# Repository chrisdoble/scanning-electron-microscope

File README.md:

This repository contains my DIY scanning electron microscope project.

My initial goal is to image samples using secondary electron emission and control the microscope from my computer.

I'm also documenting the process on YouTube [here](https://www.youtube.com/playlist?list=PLmlXFuUXRl5AR0MqcsTuL44zxy5YJyGKN).

# Roadmap

- [x] Purchase vacuum equipment
  - Edwards ADC MkII gauge controller
  - Edwards WRG-S wide range pressure gauge
  - Pfeiffer TC-600 turbomolecular pump controller
  - Pfeiffer TMH 071 P turbomolecular pump
- [x] Build a controller for the vacuum equipment
- [ ] Build a filament characterisation system
- [ ] Build an electron gun
- [ ] Build electrostatic or electromagnetic lenses
- [ ] Build an Everhart-Thornley detector
- [ ] ???
- [ ] Look at stuff

# Repository structure

The repository structure is as follows:

- [`controller`](controller): Contains files relating to the controller hardware that enables communication with the vacuum equipment, controls relays, etc.
- [`common`](common): A Rust crate containing code common to `firmware` and `host`.
- [`electron-gun-simulation`](electron-gun-simulation): A web-based simulation of an electron gun.
- [`filament-characterisation`](filament-characterisation): Contains files relating to the hardware and software used to characterise tungsten filaments to be used in the SEM.
- [`host`](host): A Rust crate containing both a library for interfacing with the controller hardware (pressure gauge, turbo molecular pump, etc.) and a binary for doing the same via a TUI.
- [`usb-tmc`](usb-tmc): A Rust crate containing an implementation of the [USB Test and Measurement Class](https://www.usb.org/document-library/test-measurement-class-specification) for interfacing with oscilloscopes, power supplies, etc.

# Required hardware

- A [Rigol DHO-814 oscilloscope](https://core-electronics.com.au/rigol-dho-814-oscilloscope.html)
- A [Rigol DP-932E power supply](https://core-electronics.com.au/rigol-dp-932e-triple-output-dc-power-supply.html)
- The custom controller as detailed in the [`controller`](controller) directory.
- The vacuum equipment mentioned above

# Running

See each directory's `README.md` for instructions.

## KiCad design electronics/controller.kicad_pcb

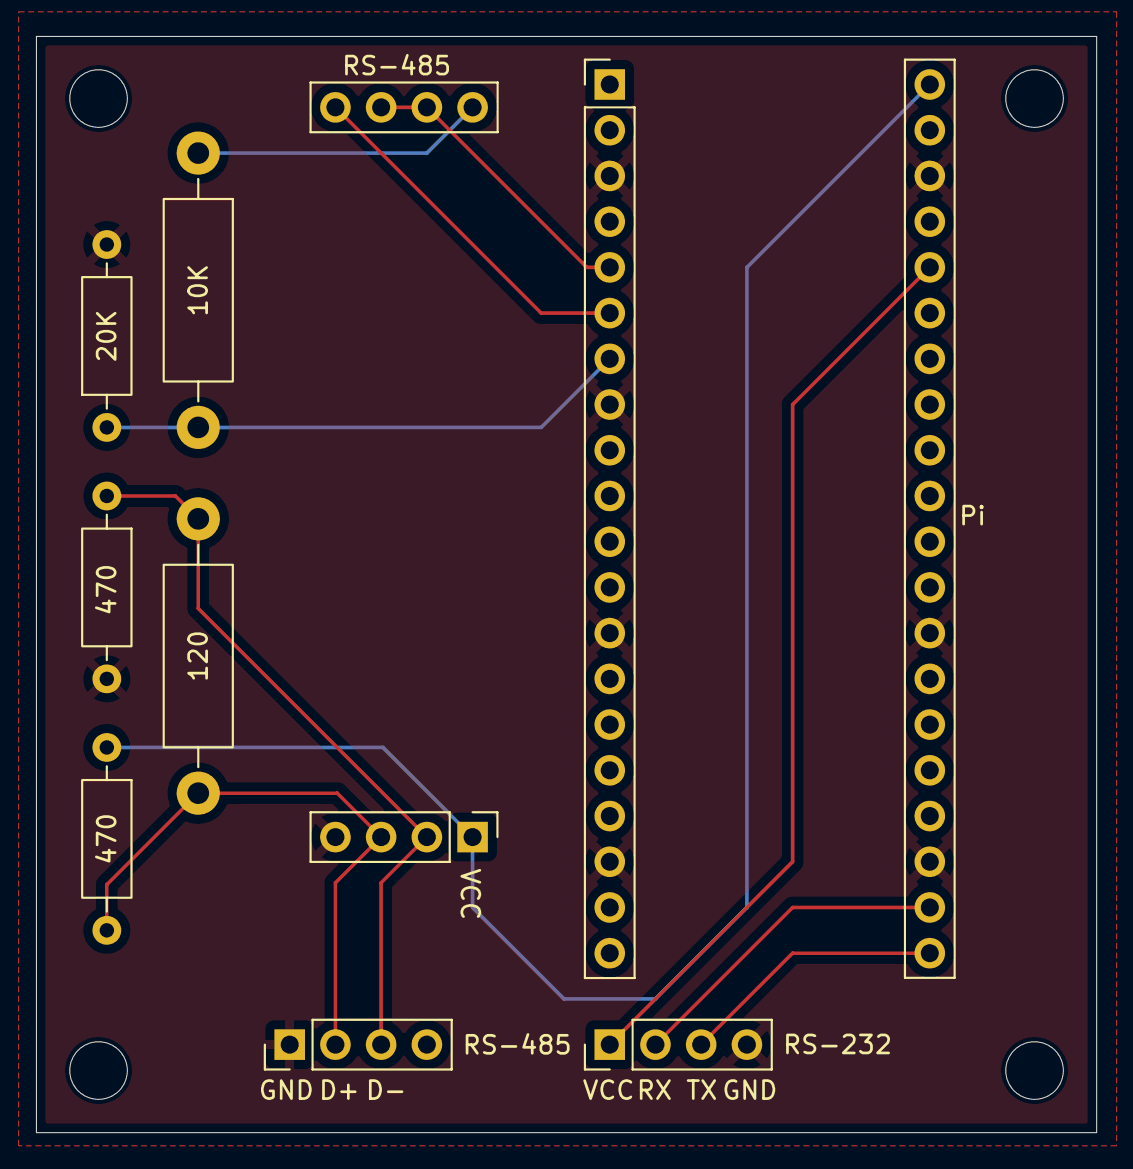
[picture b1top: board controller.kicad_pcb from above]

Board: 2 copper layers, 58.9 x 60.9 mm, 9 parts (0 on the bottom side), 11 nets.

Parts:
10K: 10k; R_Axial_DIN0411_L9.9mm_D3.6mm_P15.24mm_Horizontal
20K: 20k; R_Axial_DIN0207_L6.3mm_D2.5mm_P10.16mm_Horizontal
120: 120; R_Axial_DIN0411_L9.9mm_D3.6mm_P15.24mm_Horizontal
470, 470#2: 470; R_Axial_DIN0207_L6.3mm_D2.5mm_P10.16mm_Horizontal
Pi: Raspberry Pi Pico 2; Raspberry_Pi_Pico_2_male_headers
RS-232: UART to RS-232 converter; PinHeader_1x04_P2.54mm_Vertical
RS-485: RJ45 Jack; PinHeader_1x04_P2.54mm_Vertical
RS-485#2: UART to RS-485 converter; UART_to_RS_485_converter

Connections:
+3.3V: Pi.36 (3V3), RS-232.1 (VCC)
+5V: 470.1, Pi.40 (VBUS), RS-485#2.1 (VCC)
GND: 20K.2, 470#2.2, Pi.3 (GND), Pi.8 (GND), Pi.13 (GND), Pi.18 (GND), Pi.23 (GND), Pi.28 (GND), Pi.38 (GND), RS-232.4 (GND), RS-485.1 (GND), RS-485#2.4 (GND)
unnamed: Pi.5 (GPIO3), RS-485#2.6 (RE), RS-485#2.7 (DE)
unnamed: Pi.6 (GPIO4), RS-485#2.8 (DI)
unnamed: 10K.2, 20K.1, Pi.7 (GPIO5)
unnamed: Pi.21 (GPIO16), RS-232.3 (TXD)
unnamed: Pi.22 (GPIO17), RS-232.2 (RXD)
unnamed: 120.1, 470.2, RS-485.2 (D+), RS-485#2.3 (A)
unnamed: 120.2, 470#2.1, RS-485.3 (D-), RS-485#2.2 (B)
unnamed: 10K.1, RS-485#2.5 (RO)

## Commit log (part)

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2025-11-28 Support controlling the Edwards ADC MkII
2025-12-02 Set up the Raspberry Pi Debug Probe and defmt logging
2025-12-03 Update Embassy dependencies to use a revision containing my fix
2026-01-06 Proxy messages from the USB host to the ADC and TMP
2026-01-08 Set up workspace, move error type to a common crate
2026-01-09 Introduce host crate with initial Controller implementation
2026-01-09 Add destination argument to Controller::send_command
2026-01-09 Format error responses using Display and Write
2026-01-09 Parse errors in responses
2026-01-10 Rename common::Error to common::ControllerError
2026-01-11 Make Controller use strings instead of u8 arrays
2026-01-12 Add Adc struct
2026-01-13 Add Tmp struct
2026-01-20 Graph and log pressure over time
2026-01-21 Force graph to refresh in VS code, graph time in minutes, prevent invalid files on termination
2026-01-25 Add controller PCB design
2026-01-27 Restructure the repository, update the README
2026-01-27 Set up build123d for the controller case
2026-02-03 Revert "Set up build123d for the controller case"
    This reverts commit 3bbeb0c9e4b1fe31b4117f66bcf109ab93aa7ac6.
2026-02-03 Add 3D models of the controller case
2026-02-03 Tweak case to reduce printing time
2026-02-06 Make micro USB B port hole bigger
2026-02-06 Refactor host crate to contain both a binary and a library
2026-02-12 Implement demo vacuum system control application
2026-04-20 Fix clippy warnings
2026-04-21 Add specification documents for electron gun simulation
2026-04-22 Add scaffolding for electron gun simulation
2026-04-22 Add solver types and stub API
2026-04-23 Add wasm-api types and stub API
2026-04-23 Call wasm from web app
2026-04-24 Add slider UI
2026-04-25 Move computation to a web worker
2026-04-27 Add the visualisation canvas and render a test electrode
2026-04-28 Implement SOR solver
2026-04-29 Render the potential field using the Turbo colour map
2026-04-29 Rasterise the electron gun
2026-04-29 Draw a voltage legend
2026-05-10 Update documents to describe direct solve method
2026-05-10 Move to direct solve method
2026-05-11 Render low resolution solution while changing parameters
2026-05-11 Render voltage legend outside solution canvas
2026-05-11 Render a preview solution first when the app is opened
2026-05-11 Add zooming and panning
2026-05-11 Calculate electric field
2026-05-11 Draw the electric field
2026-05-12 Simplify render functions, add potential / electric field toggles
2026-05-13 Compute beam trajectories
2026-05-13 Add option to flip electric field arrows
2026-05-13 Increase small arrow size, start trajectories in the middle of cells
2026-05-21 Don't render the TUI so frequently
2026-05-25 Update READMEs
2026-05-26 Allow toggling the Wehnelt cylinder and anode
2026-05-26 Change electrode test to intersection rather than containment to support smaller filament sizes
2026-05-26 Reduce solution area margin to speed up calculations
2026-05-26 Improve default geometry values
2026-05-27 Add link to YouTube playlist in README
2026-05-28 Calculate the trajectories of 4 electrons per cell
2026-06-10 Add a Python script to connect to my oscilloscope via USB and print its ID
2026-06-10 Update the Python script to read the average voltage of channel 1 on the scope
2026-06-11 Port oscilloscope script to Rust
2026-06-13 Add a script to connect to and control my power supply
